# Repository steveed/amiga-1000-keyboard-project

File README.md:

# amiga-1000-keyboard-project
An open source replacement PCB for the Commodore Amiga 1000 keyboard.

The switch plate, generated from the PCB (1.2 mm FR4, version 1):

Renders are regenerated by GitHub Actions whenever the board or plate changes.

## Project Goals
1. Provide a drop-in replacement keyboard PCB for original Amiga 1000 machines.

## Controller
The board takes the original Amiga 1000 keyboard controller (a mask-ROM 6500/1). A 6570 from an
A500/A2000/A3000 keyboard also works if KCLK and KDAT are swapped: solder the cable's white and green
wires into each other's pads on J1. With the original controller: white = KCLK (PA0, pin 38),
green = KDAT (PA1, pin 37), red = +5V, black = GND.

## Rev 2
A second board for the same case that needs no donor controller: an ATmega32U4 with open firmware,
surface-mount parts assembled by the fab, Cherry MX switches, and both the Amiga cable and USB-C
live at once. The first boards have been programmed, and an assembled prototype is fully tested
over USB. See [docs/rev2.md](docs/rev2.md).

## Building
Everything runs in Docker through `make` (KiCad 10 and a small Python image):

- `make print` - 1:1 print sheets in `build/print/` (one 11x17 sheet, or two Letter sheets to tape together).
  Print at 100% / Actual size and check the 100 mm bar.
- `make drc` - refill the pours and fail on any DRC error or schematic/board mismatch.
- `make bom` - regenerate `pcb/bom.csv` from the schematic's Part fields.
- `make fab` - gerbers and drill files, zipped in `build/fab/`.
- `make plate` - the switch plate (DXF and a gerber zip for FR4) in `build/plate/`, generated from the PCB.
- `make case` - the printable case (four STLs and a preview) in `build/case/`, from `case/a1000_case.scad`, for rev 2 (`REV=1` for rev 1). `make case-spacers` fits a rev 2 board in a rev 1 case. See [case/README.md](case/README.md).
- `make keycaps` - rev 2's keycaps in the A1000's sizes (Return, Shifts, `~`, Backspace, Tab; STLs) in `build/case/`, from `case/a1000_keycaps.scad`.
- `make rev2-sch`, `make rev2-pcb`, `make rev2-route`, `make rev2-drc` - the rev 2 board (ATmega32U4, surface mount, Cherry MX). See [pcb/rev_2/README.md](pcb/rev_2/README.md).
- `make firmware`, `make firmware-test` - the rev 2 firmware and its unit tests. See [firmware/README.md](firmware/README.md).
- `make render` - the README renders in `build/render/`.
- `make release` - all of the above, collected in `build/release/`.
- `make rev2-release` - rev 2's order files, plates and firmware, collected in `build/rev2-release/`.

Pushing a `v*` tag runs `make release` on GitHub and publishes rev 1's files as a GitHub release;
pushing a `rev2-v*` tag does the same for rev 2 with `make rev2-release`.

## Reference Material
- [docs/amiga-a1000-schematics-all.pdf](docs/amiga-a1000-schematics-all.pdf) - Amiga 1000 schematics

## Credits
Future revisions are expected to reuse parts of Henryk Richter's [A500KB](https://github.com/HenrykRichter/A500KB) mechanical keyboard. This project uses the same license so that work can be incorporated.

## License
The PCB, its design files and all support code are licensed under [Creative Commons Attribution-NonCommercial-ShareAlike 4.0 International (CC BY-NC-SA 4.0)](https://creativecommons.org/licenses/by-nc-sa/4.0/). See [LICENSE.txt](LICENSE.txt) for the full text.

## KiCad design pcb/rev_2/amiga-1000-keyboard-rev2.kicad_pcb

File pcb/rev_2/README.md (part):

# Rev 2

A surface-mount version of the board that the fab can assemble from stocked parts, for Cherry MX
switches; only the keyswitches and the Caps Lock LED (which sits inside its switch) are fitted by hand. Rev 1, the
through-hole recreation of the original that takes the original 6500/1 controller, stays in `pcb/`.

The outline, mounting holes and switch positions match rev 1, so the case fits both boards; rev 2
needs its own MX plate.

## Schematic

`amiga-1000-keyboard-rev2.kicad_sch` is generated by `tools/gen_rev2_sch.py`: edit the script and
run `make rev2-sch`, which regenerates it and runs ERC. The switches keep rev 1's references and
key names.

- **Controller:** ATmega32U4 at 16 MHz, in place of the mask-ROM 6500/1. Its firmware is
  ported from Henryk Richter's [A500KB](https://github.com/HenrykRichter/A500KB) (AVR, same licence).
  Flashing:
  - first time: the 32U4 ships with Microchip's USB (DFU) bootloader, and a chip with empty flash
    runs straight into it, so it can be flashed over USB as it comes (confirmed on the first boards);
  - updates: the firmware jumps to the bootloader on a key combination, then flash over USB;
  - recovery, if the firmware can't get there: short JP2 (BOOT) while shorting JP1 (RESET), then
    flash over USB; or use the 6-pin ISP header (J3, not fitted; a pogo adapter or a soldered header
    and any AVR programmer), which works even without the bootloader.
- **Amiga and USB both live:** the Amiga cable (J1, same pin order as rev 1's J1: GND, +5V, KCLK,
  KDAT) and a USB-C socket (J2) are on every board. The keyboard works on either, or both at once. Plugging
  both in is safe: the TPS2116 keeps the two 5 V supplies apart (no back-feeding either way), and the
  firmware only pulls KCLK and KDAT while the Amiga's 5 V is present. With both connected, the
  Amiga's and the PC's grounds are joined through the keyboard, as with any USB device.
- **Power:** a TPS2116 power mux. The Amiga's 5 V has priority; USB takes over when it's absent
  (below about 4.3 V), with no diode drop. Its status output (AMIGA_PWR, on PE6) tells the firmware
  whether the Amiga is powered, so it never pulls KCLK or KDAT on a switched-off machine.
- **USB:** USBLC6-2SC6 ESD protection, a 500 mA resettable fuse, 22 R series resistors and the
  5.1 k CC resistors that make it a USB-C device.
- **Matrix:** 8 rows x 12 columns, one diode per key, so any combination of keys reads correctly.
  Each physical row's first 12 keys take electrical rows 0-5; the rest fill rows 6 and 7. SW55
  and SW58 (the international keys) get their own positions; SW92 (short ISO left shift) is fitted
  instead of SW87 and shares its position.

## Switches

Rev 2 takes Cherry MX (and compatible) switches; rev 1 is the Mitsumi replacement. The footprints
come from `tools/gen_mx_fp.py`, in the standard orientation (pins north, LED holes south), with
PCB-mount pegs. Keycap widths come from rev 1's switch spacing. Keys of 2U and wider have PCB-mount
stabiliser holes; the space bar (7.5U) uses a 7U stabiliser (114.3 mm). Return follows Henryk
Richter's US Return for the A500KB: the switch at the key's stem, the centre of the column the cap
has on both rows, with a vertical 2U stabiliser. It suits the US inverted L and the international
Return alike.

SW87 (US 2.5U left Shift) and SW92 (ISO 1.5U short Shift) are alternatives under the same keycaps.
Their facing pegs would be 0.54 mm apart, so SW87 has no west peg and SW92's east peg is a slot
either switch's peg fits.

The Caps Lock LED (D92) is a 3 mm LED through the Caps Lock switch, fitted by hand with it.

## Board

`amiga-1000-keyboard-rev2.kicad_pcb` is generated, then routed:

- `make rev2-pcb` (`tools/gen_rev2_pcb.py`) builds it from rev 1's board and the rev 2 schematic:
  rev 1's outline, stack-up, design rules and GND pours, with rev 2's footprints linked to the
  schematic and placed. The file comes out the same on every run (footprints in reference order,
  UUIDs derived from references), which matters because the router's result depends on file order.
- `make rev2-route` routes it with [KiCadRoutingTools](https://github.com/drandyhaas/KiCadRoutingTools)
  (`tools/route_rev2.py`), following the passes in `tools/rev2_route.json`, then removes the vias
  and tracks left dangling (`tools/rev2_cleanup.py`).
- `make rev2-drc` checks it, schematic parity included.

Placement and routing notes:

- Switches sit at rev 1's key centres; Return at its stem.
- Each key's diode is on the back, between its row and the next, at the first spot that clears every
  pad and hole by 0.5 mm.
- The controller, USB-C and power parts are on the strip behind the keys. USB-C opens to the rear on
  the strip's back edge, about 31 mm right of the case's jack, through its own opening in the
  printed case's back wall. On the first boards it opened to the left out of the step, and the
  plug ran into the jack. The Amiga header (J1) sits on the board's back edge behind the jack.
- U1 sits on the right of the strip, where rev 1's controller was, so the matrix lines run along the
  strip instead of converging mid-board. It's turned so its row pins face the keys, and fanned out: every pin but the crystal and USB data
  pins has a short track to its own via, on two staggered rings. About 20 matrix lines converge on
  this 0.8 mm-pitch chip on two layers, and the router reaches a ring of vias far more easily than
  the pads. A few decoupling caps sit on the back, under it (the diodes already make it a two-sided
  assembly).
- The TPS2116's VIN2 and GND pins have pre-routed escapes too: they're 0.5 mm-pitch pins the router
  kept falling just short of.
- Routing order matters (see `tools/rev2_route.json`): ROW5, the longest run into U1, goes first;
  then VBUS; then the USB and power nets at 0.2 mm clearance (their 0.5 mm-pitch pins are too tight
  for 0.25); then the other rows; then everything else at 0.25 mm, which keeps tracks clear of the
  MX holes; then GND.
- `amiga-1000-keyboard-rev2.kicad_dru` allows the overlaps that are meant (the left Shift
  alternatives, the Caps Lock LED inside its switch, the plate screws between switches) and one
  thermal spoke on GND pads.

### KiCadRoutingTools

`make rev2-route` runs in a `krt:local` image built from a KiCadRoutingTools checkout, with its Rust
router built inside it:

```
FROM python:3.12-slim
WORKDIR /krt
COPY requirements.txt .
RUN pip install --no-cache-dir -r requirements.txt
COPY . .
RUN rm -f rust_router/*.so && python3 build_router.py
```

Build it from the checkout (`docker build -f <that Dockerfile> -t krt:local .`). Routing takes about
five minutes.

## Ordering from JLCPCB

Every push to `main` that touches rev 2 runs the "Rev 2 for JLCPCB" GitHub workflow: DRC and
schematic parity, then gerbers, BOM and placement, uploaded as the artifact
`amiga-1000-keyboard-rev2-jlcpcb`. Locally, `make rev2-fab rev2-jlc` writes the same files to
`build/rev2-fab/` and `build/rev2-jlc/`. Pushing a `rev2-v*` tag publishes the same files, the plates
and the firmware hex as a GitHub release (`make rev2-release`).

- **PCB:** upload `amiga-1000-keyboard-rev2-gerbers.zip`. Two layers, 1.6 mm.
- **Assembly:** both sides (the key diodes and two of U1's decoupling caps are on the back). Upload
  `bom-jlc.csv` and `cpl-jlc.csv`, then check the placement preview: the rotation corrections in
  `tools/jlc_export.py` cover the ICs, but check every part's orientation, especially the diodes and
  U1-U3, before ordering.
- **Parts:** 123 parts in 18 lines, LCSC numbers checked against JLCPCB's parts library. Six are
  Extended parts with a setup fee each (U1, U2, U3, J1, J2 and F1); the rest, all the passives and
  the crystal included, are Basic. The crystal is a 9 pF-load part, so its load caps are 12 pF.
- **Plate:** `amiga-1000-keyboard-rev2-plate-us-gerbers.zip` or `...-plate-iso-gerbers.zip`, as a
  second PCB order: 1.6 mm FR4, no copper needed (the gerbers carry only the outline and mask).
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
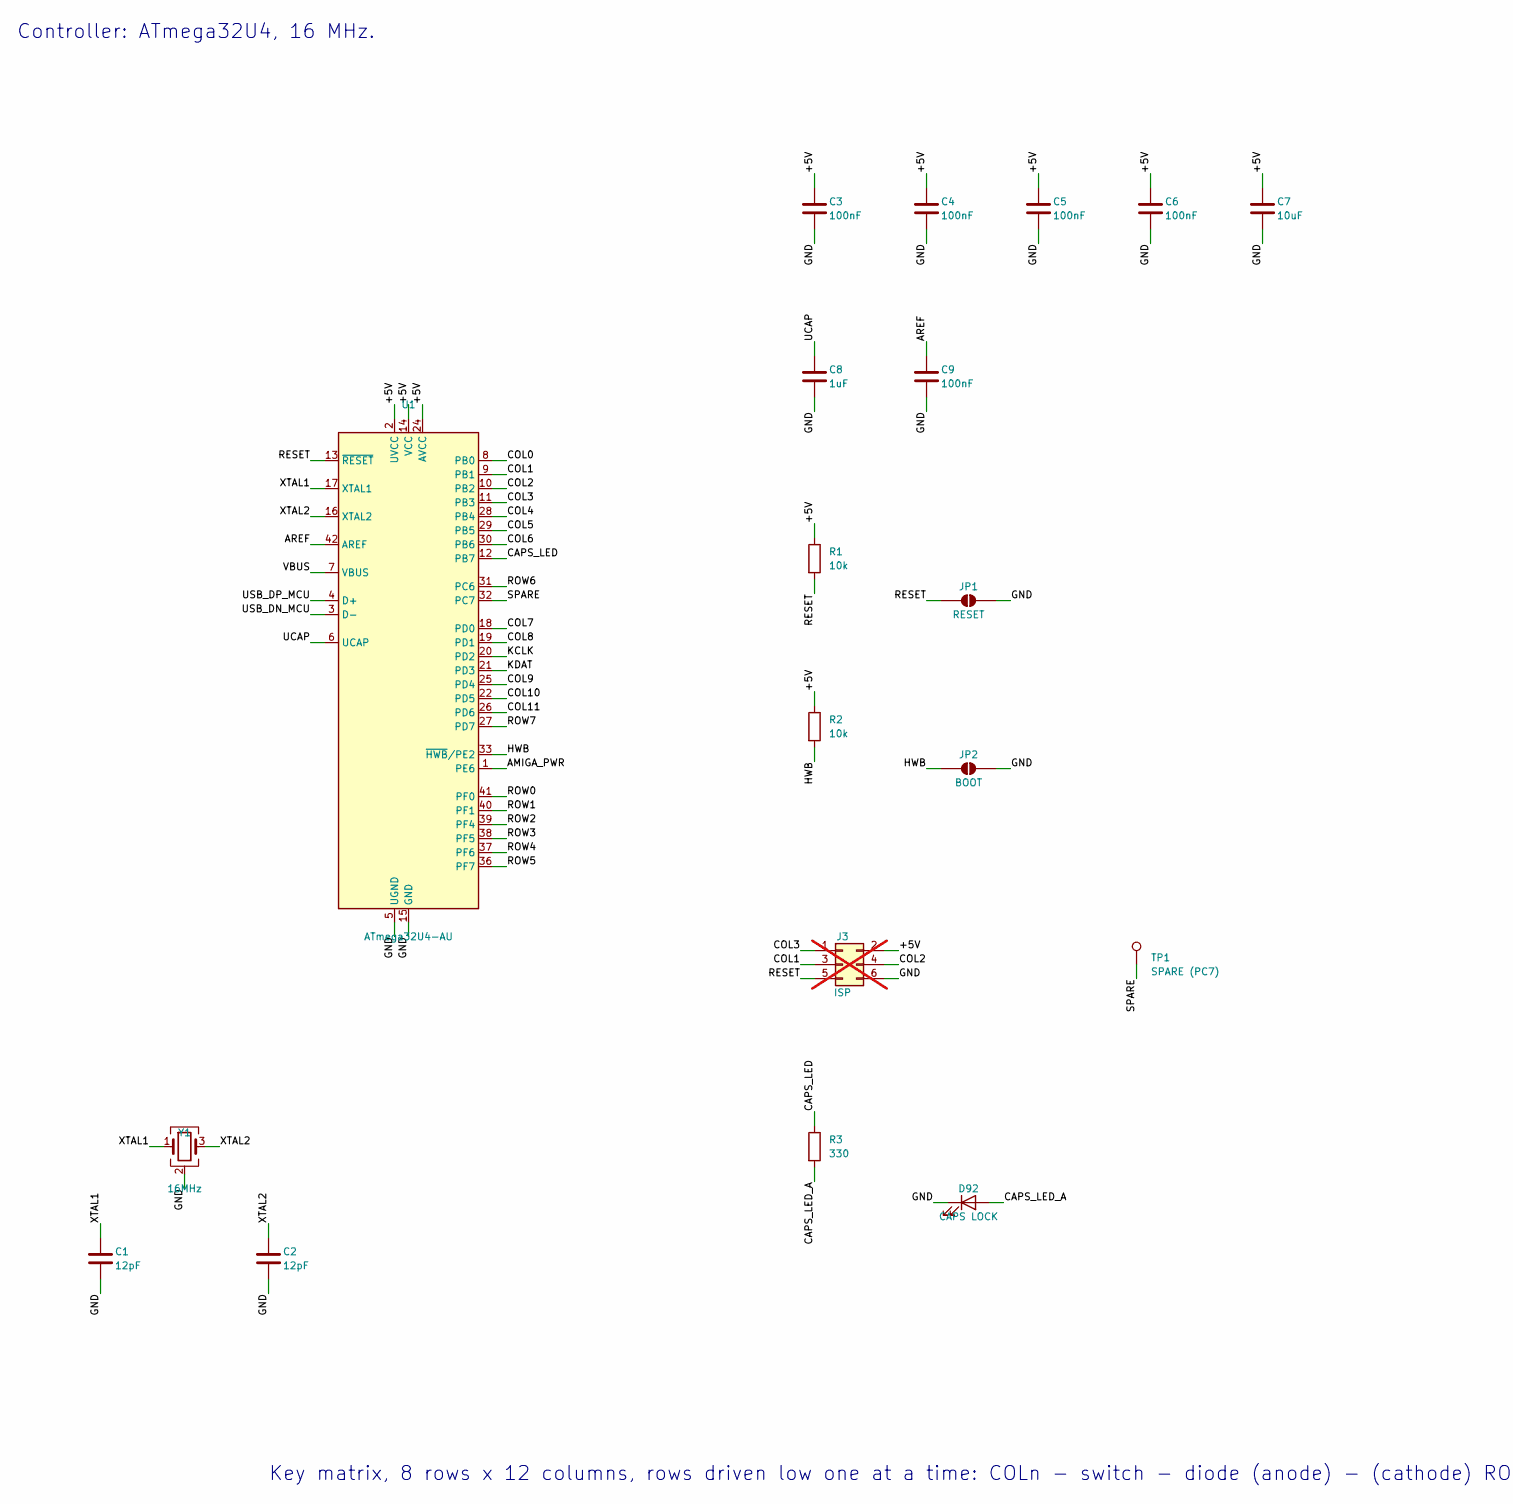
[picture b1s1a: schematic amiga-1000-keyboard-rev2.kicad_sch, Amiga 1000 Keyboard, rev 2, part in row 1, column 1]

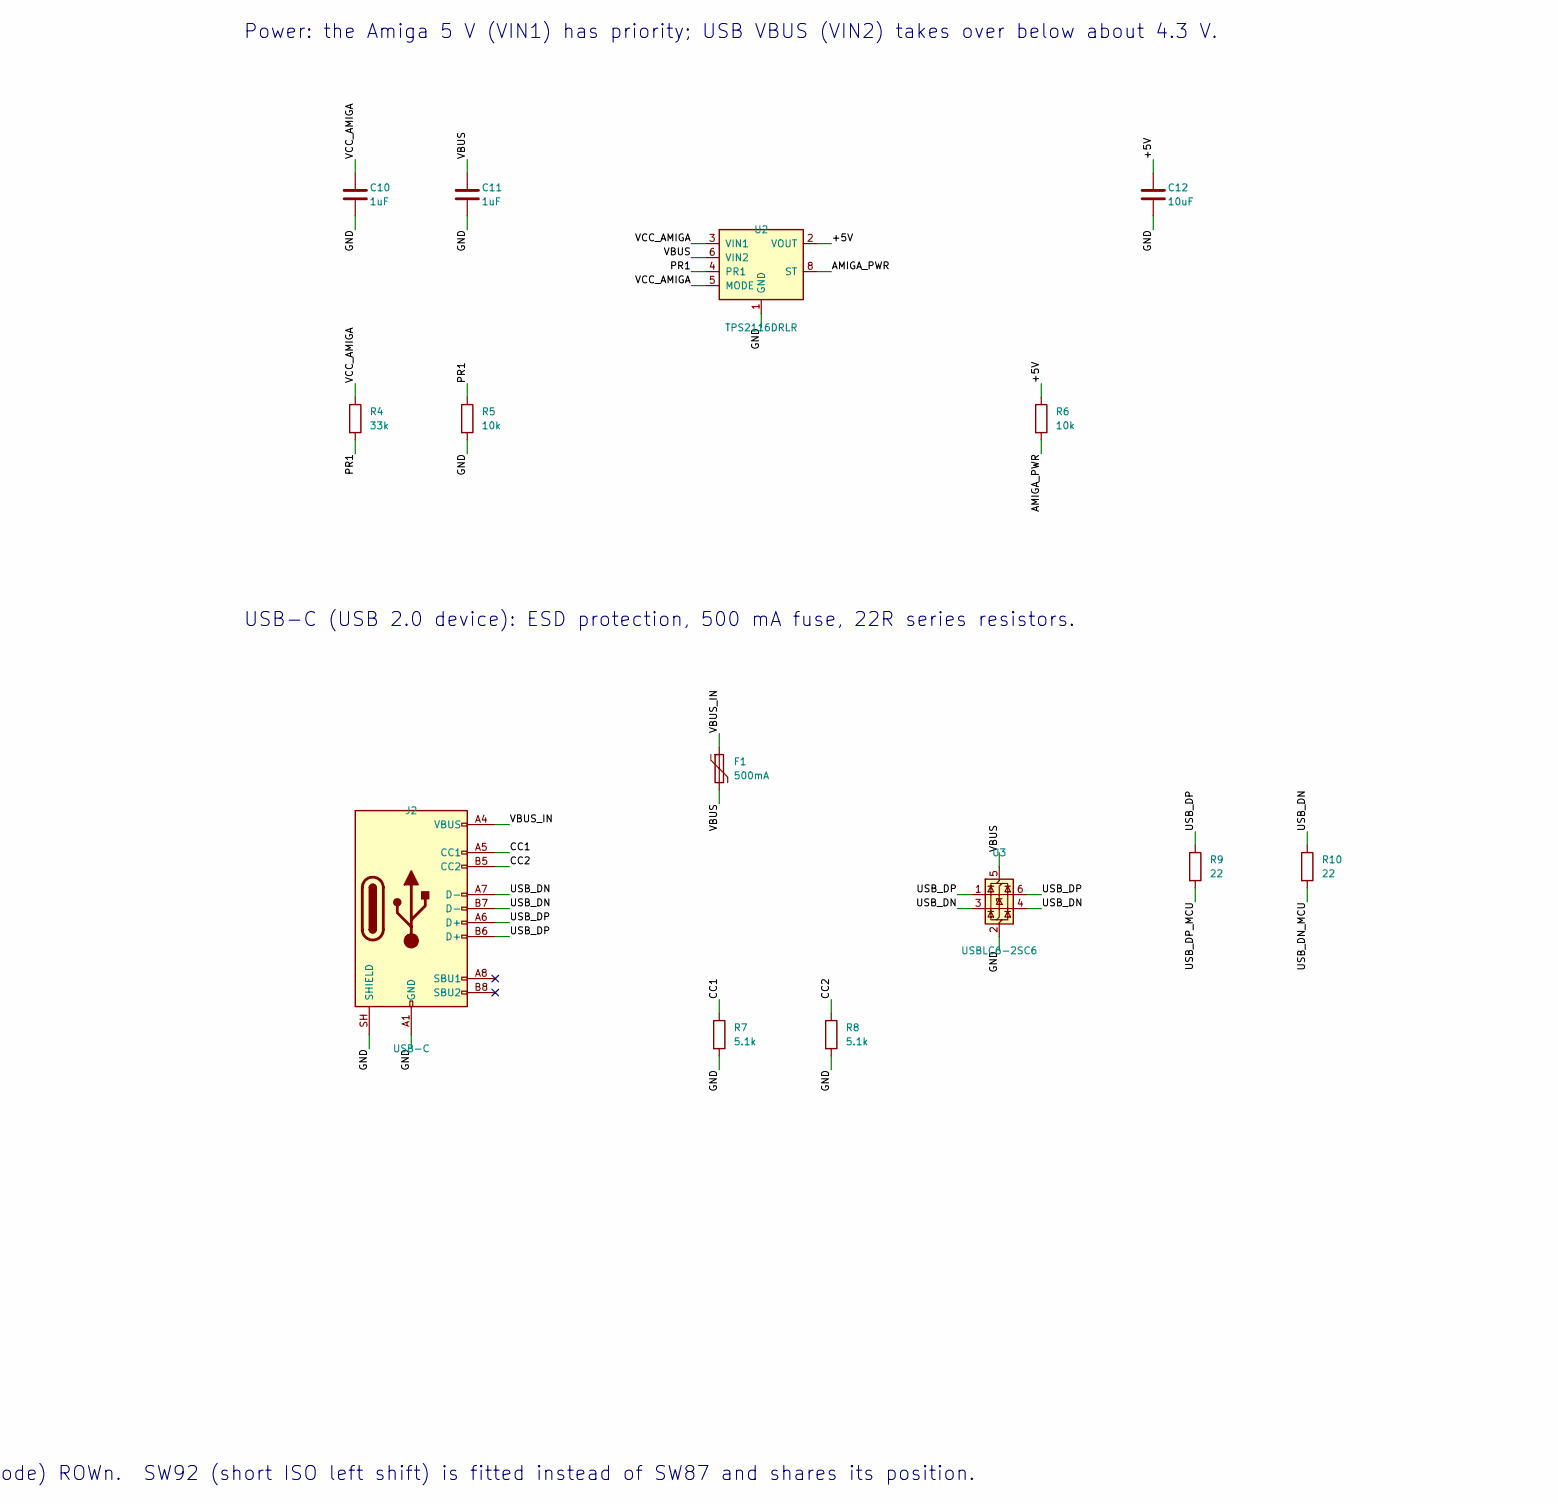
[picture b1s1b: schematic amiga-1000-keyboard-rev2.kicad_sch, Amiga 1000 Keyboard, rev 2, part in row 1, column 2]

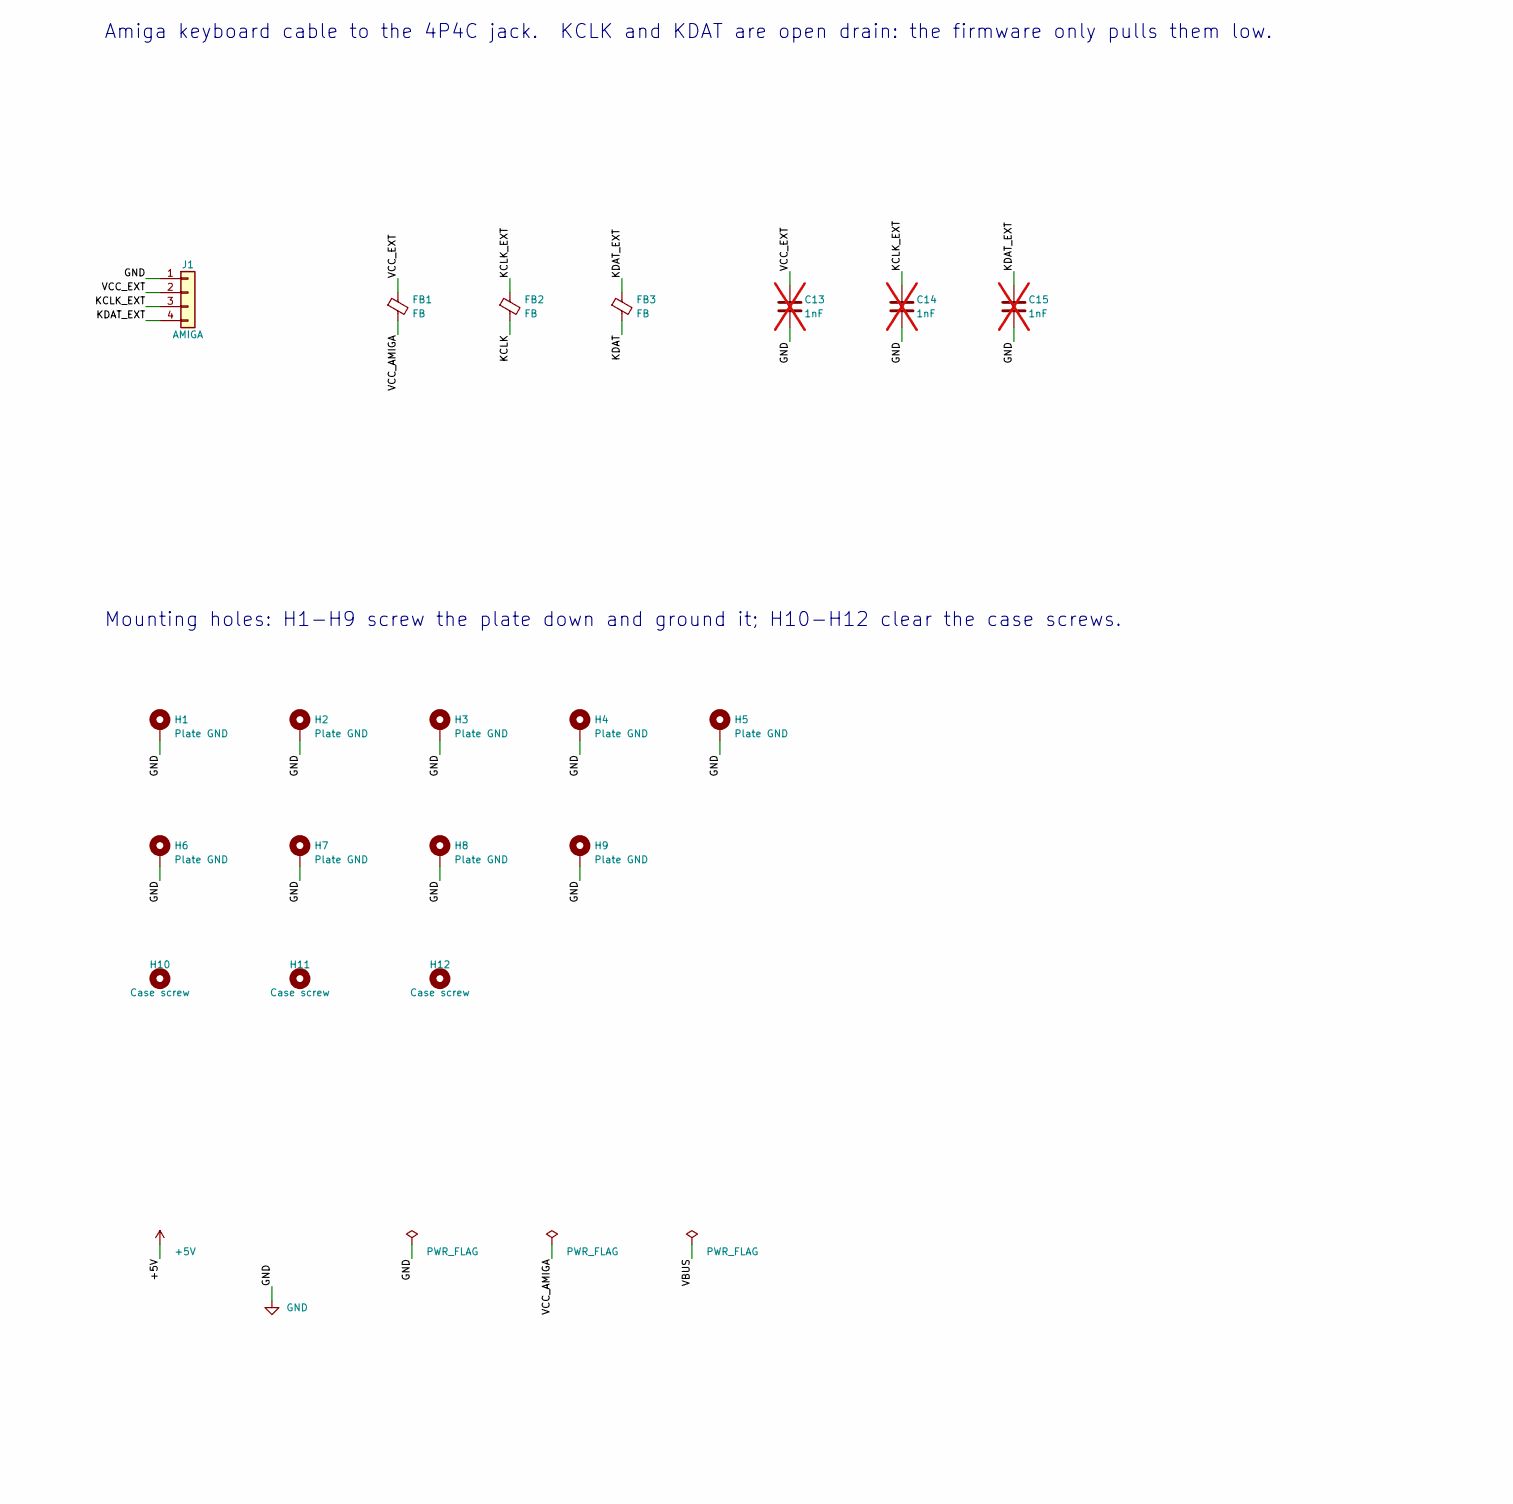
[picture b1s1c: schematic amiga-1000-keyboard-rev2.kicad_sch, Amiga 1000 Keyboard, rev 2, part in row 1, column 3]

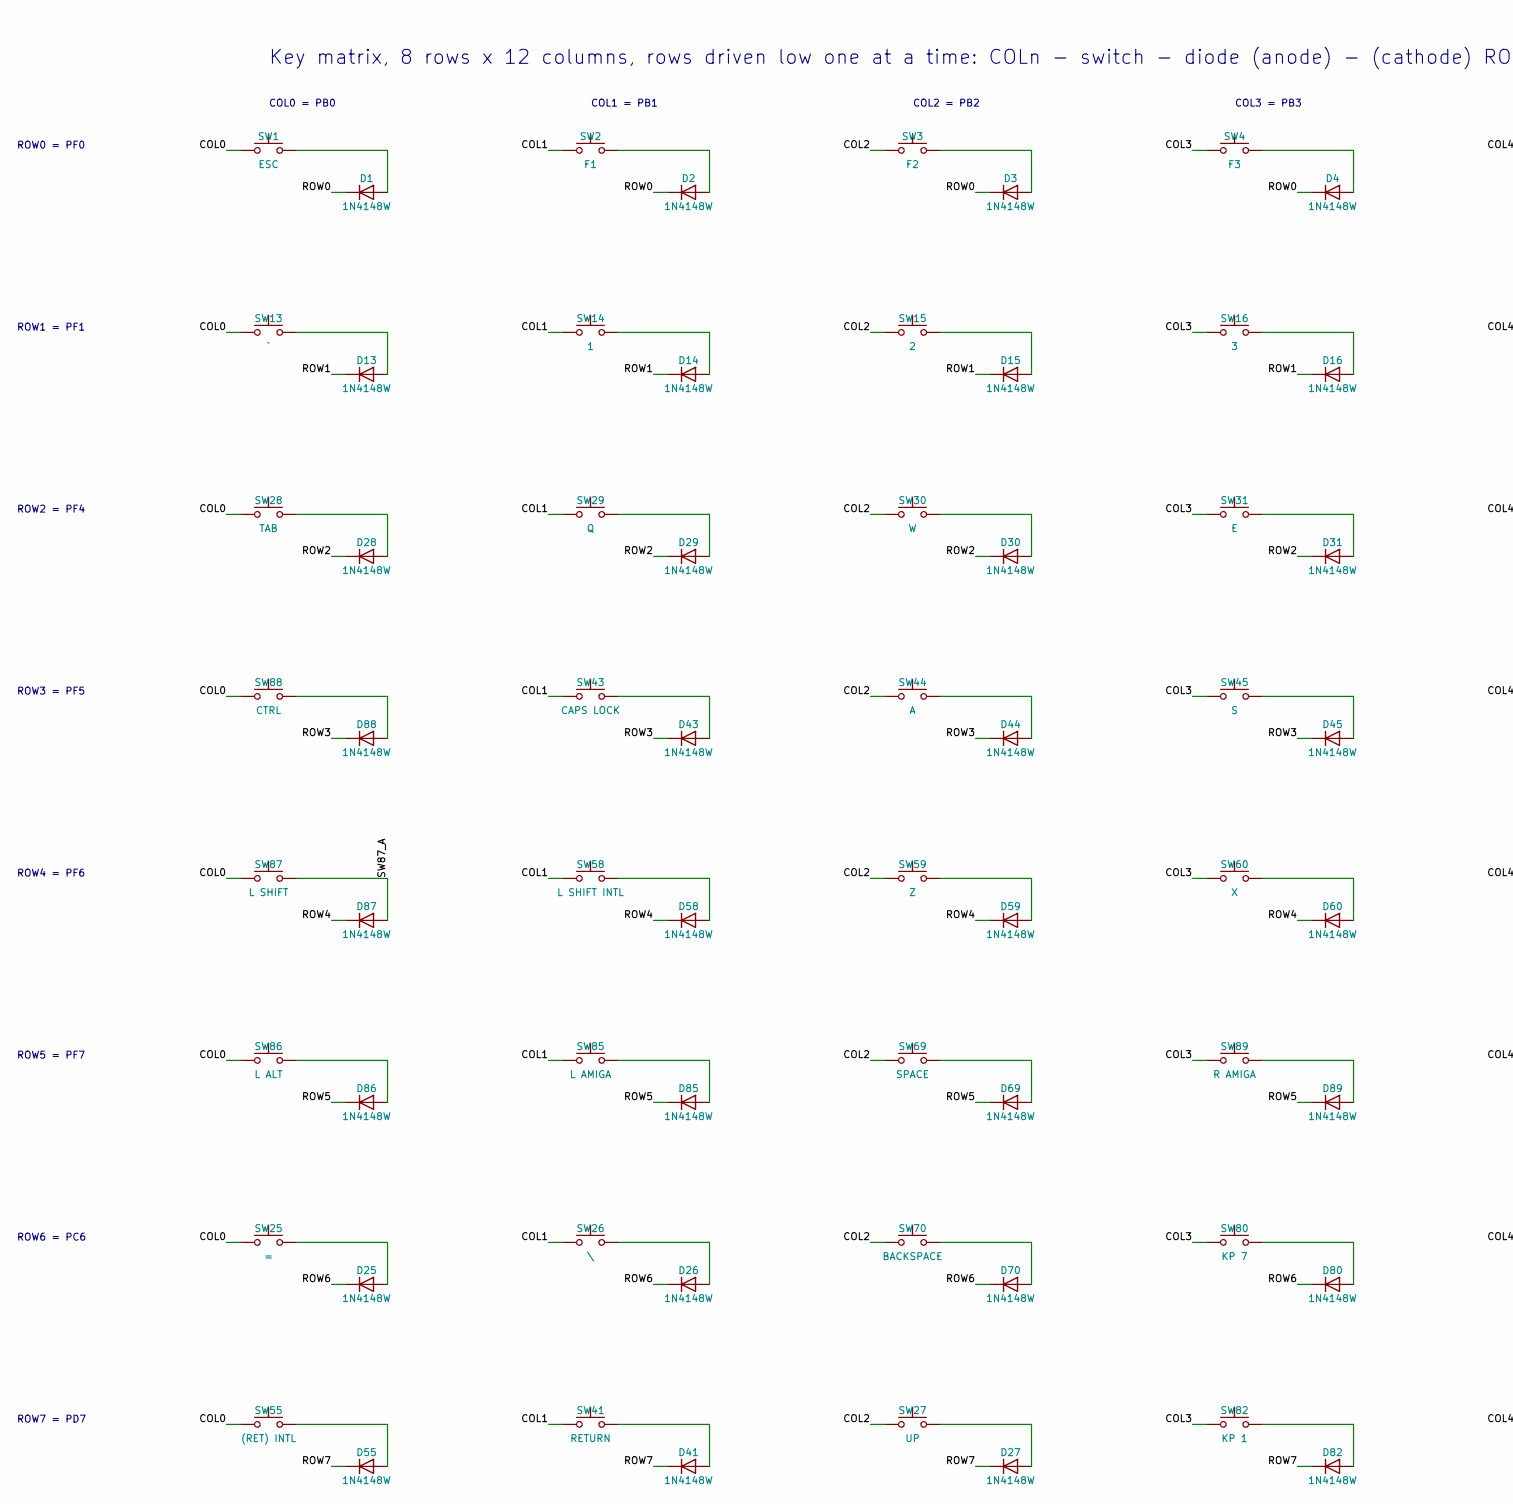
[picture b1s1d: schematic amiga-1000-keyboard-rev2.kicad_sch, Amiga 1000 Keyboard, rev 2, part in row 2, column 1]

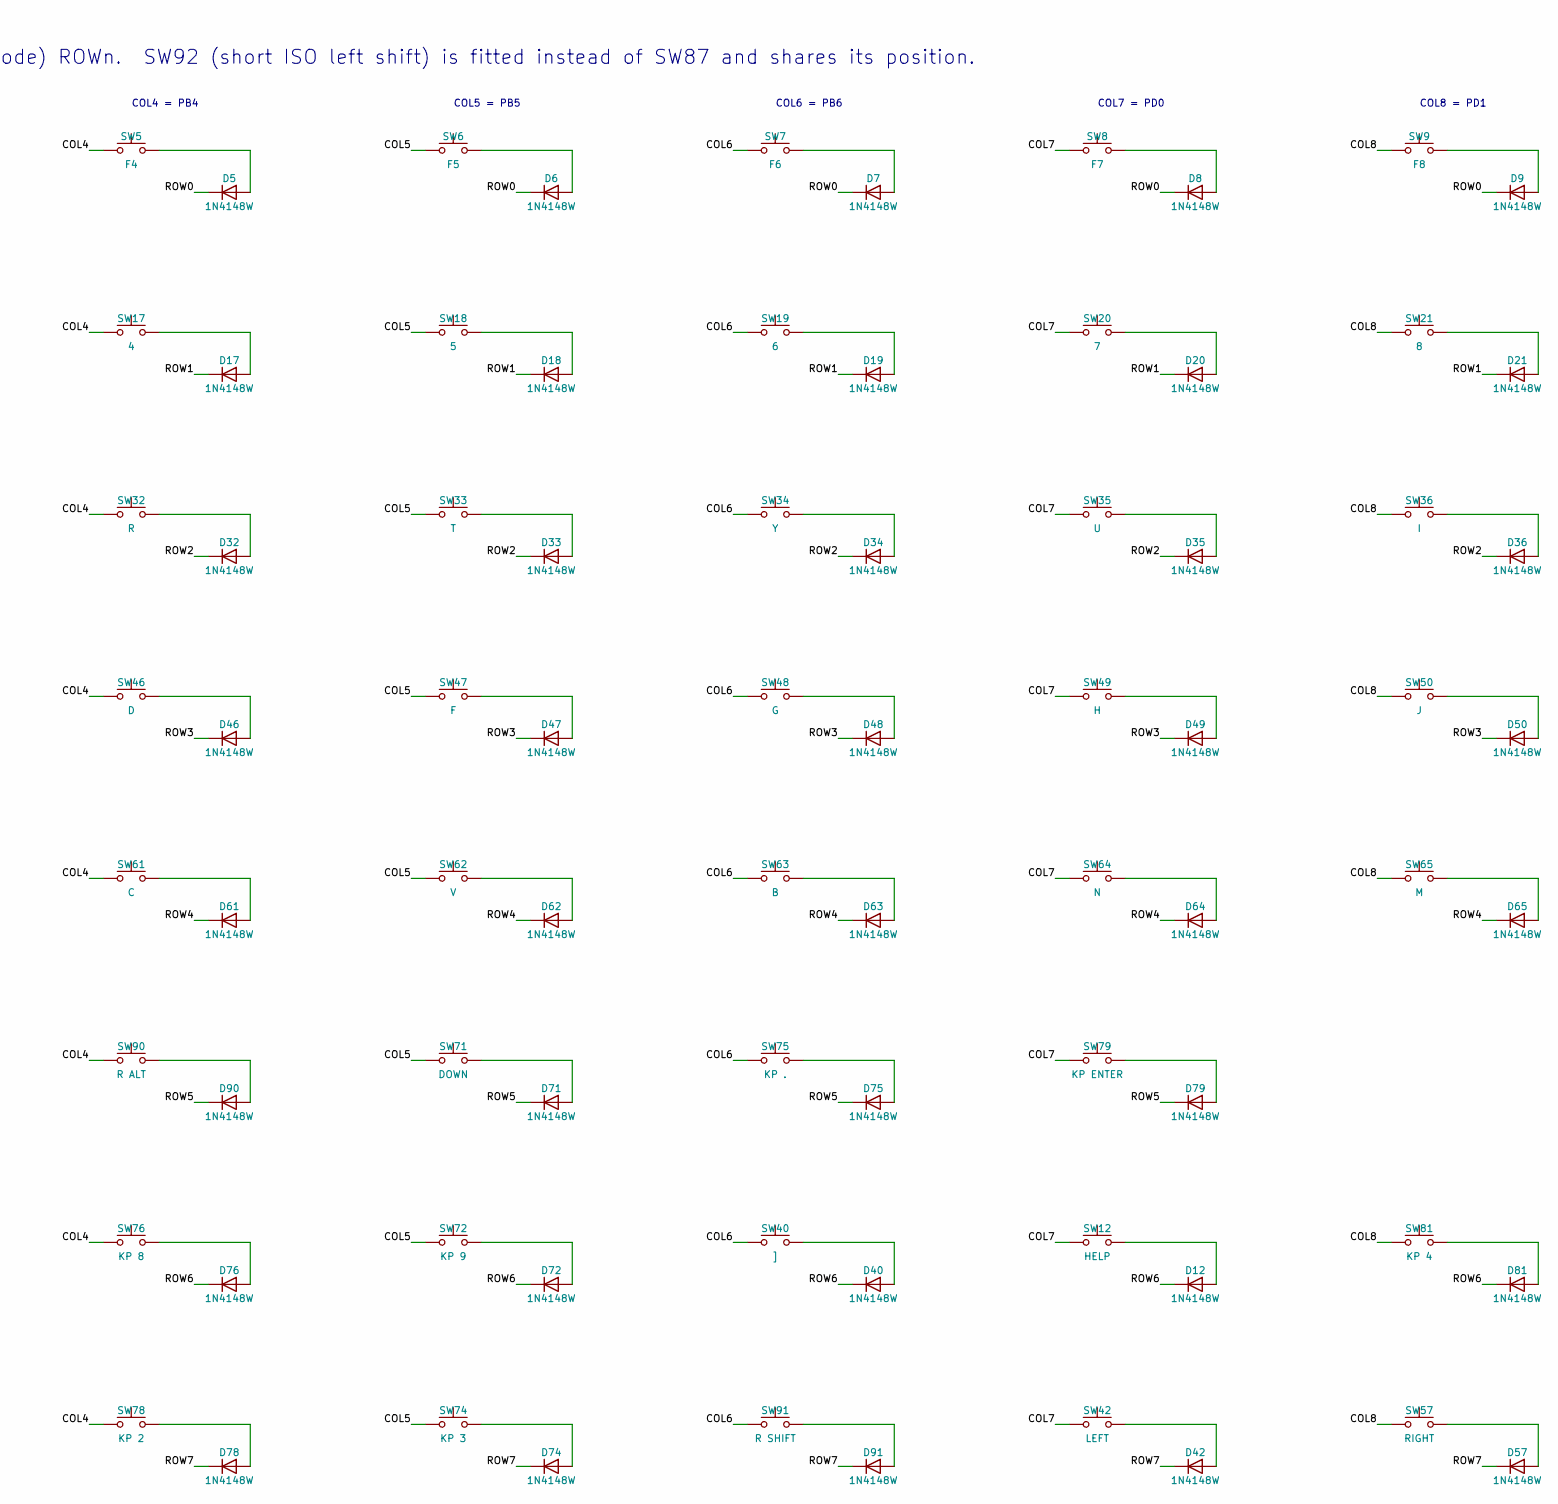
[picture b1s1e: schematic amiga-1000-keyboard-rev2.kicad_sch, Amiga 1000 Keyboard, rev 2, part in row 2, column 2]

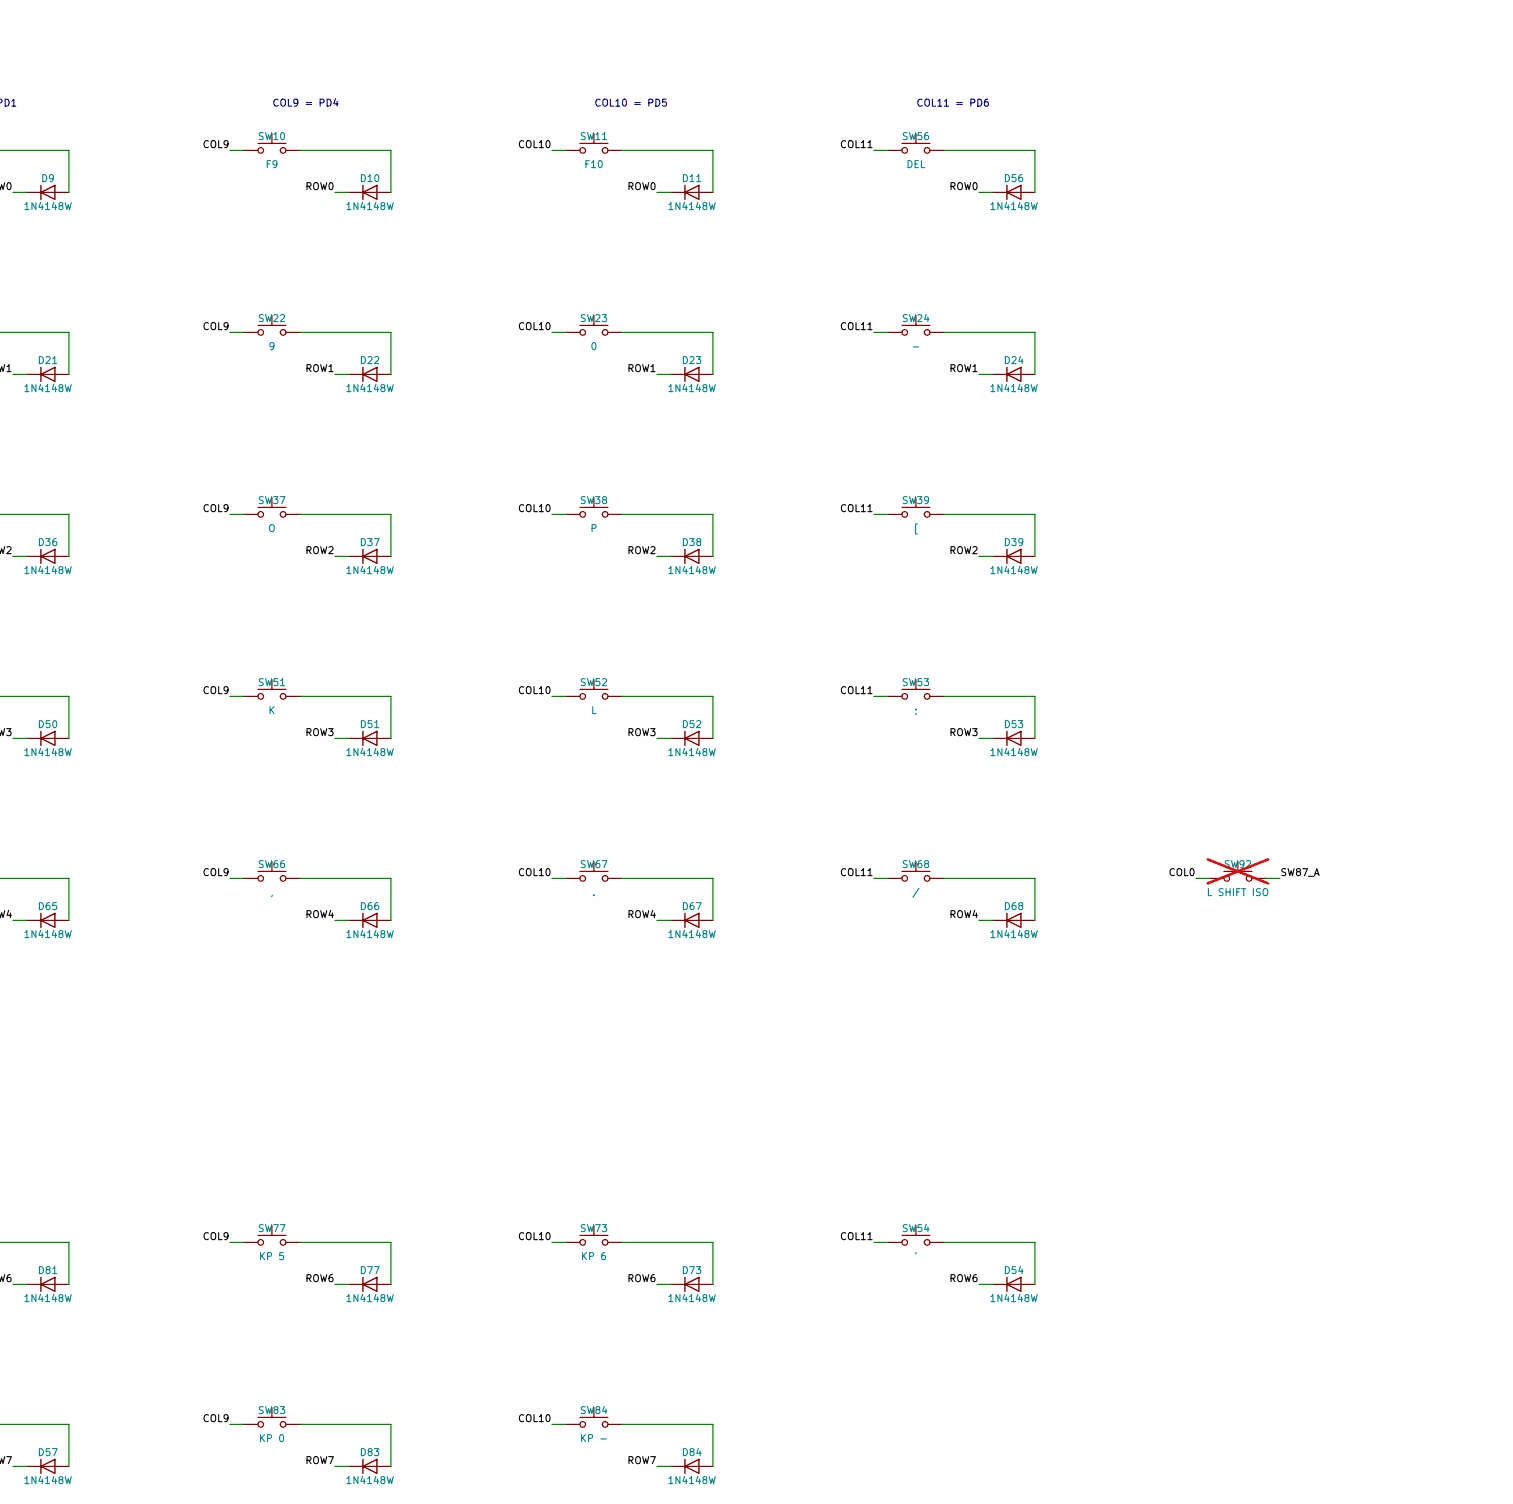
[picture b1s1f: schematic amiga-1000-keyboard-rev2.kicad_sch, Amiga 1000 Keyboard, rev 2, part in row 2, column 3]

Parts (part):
C1, C2: 12pF; C_0402_1005Metric; Part 12 pF C0G 0402; LCSC C1547
C3, C4, C5, C6, C9: 100nF; C_0402_1005Metric; Part 100 nF X7R 0402; LCSC C1525
C7, C12: 10uF; C_0603_1608Metric; Part 10 uF X5R 10 V 0603; LCSC C19702
C8: 1uF; C_0402_1005Metric; Part 1 uF X5R 0402; LCSC C52923
C10, C11: 1uF; C_0402_1005Metric; Part 1 uF X5R 10 V 0402; LCSC C52923
C13, C14, C15: 1nF; C_0402_1005Metric; Part 1 nF X7R 0402; LCSC C1523; not fitted
D1, D2, D3, D4, D5, D6, D7, D8, D9, D10, D11, D12, D13, D14, D15, D16, D17, D18, D19, D20, D21, D22, D23, D24, D25, D26, D27, D28, D29, D30, D31, D32, D33, D34, D35, D36, D37, D38, D39, D40, D41, D42, D43, D44, D45, D46, D47, D48, D49, D50, D51, D52, D53, D54, D55, D56, D57, D58, D59, D60, D61, D62, D63, D64, D65, D66, D67, D68, D69, D70, D71, D72, D73, D74, D75, D76, D77, D78, D79, D80, D81, D82, D83, D84, D85, D86, D87, D88, D89, D90, D91: 1N4148W; D_SOD-123; Part 1N4148W SOD-123; LCSC C81598
D92: CAPS LOCK; MX_A1000_LED; Part 3 mm LED through a Cherry MX switch
F1: 500mA; Fuse_1206_3216Metric; Part 500 mA hold PTC fuse, 1206; LCSC C70077
FB1, FB2, FB3: FB; L_0603_1608Metric; Part Ferrite bead 600R@100MHz 0603; LCSC C1002
H1, H2, H3, H4, H5, H6, H7, H8, H9: Plate GND; MountingHole_3.8mm_Plate_GND
H10, H11, H12: Case screw; MountingHole_7.5mm_CaseClearance
J1: AMIGA; JST_PH_S4B-PH-SM4-TB_1x04-1MP_P2.00mm_Horizontal; Part JST PH 4-pin SMD right angle; LCSC C265102
J2: USB-C; USB_C_Receptacle_HRO_TYPE-C-31-M-12; Part HRO TYPE-C-31-M-12 USB-C receptacle; LCSC C165948
J3: ISP; PinHeader_2x03_P2.54mm_Vertical; Part AVR ISP header (recovery only); not fitted
JP1: RESET; SolderJumper-2_P1.3mm_Open_RoundedPad1.0x1.5mm; Part pads, shorted with tweezers
JP2: BOOT; SolderJumper-2_P1.3mm_Open_RoundedPad1.0x1.5mm; Part pads, shorted with tweezers
R1, R2, R5, R6: 10k; R_0402_1005Metric; Part 10k 1% 0402; LCSC C25744
R3: 330; R_0402_1005Metric; Part 330 1% 0402; LCSC C25104
R4: 33k; R_0402_1005Metric; Part 33k 1% 0402; LCSC C25779
R7, R8: 5.1k; R_0402_1005Metric; Part 5.1k 1% 0402; LCSC C25905
R9, R10: 22; R_0402_1005Metric; Part 22 1% 0402; LCSC C25092
SW1: ESC; MX_A1000_1U; Part Cherry MX (or compatible) keyswitch
SW2: F1; MX_A1000_1.25U; Part Cherry MX (or compatible) keyswitch
SW3: F2; MX_A1000_1.25U; Part Cherry MX (or compatible) keyswitch
SW4: F3; MX_A1000_1.25U; Part Cherry MX (or compatible) keyswitch
SW5: F4; MX_A1000_1.25U; Part Cherry MX (or compatible) keyswitch
SW6: F5; MX_A1000_1.25U; Part Cherry MX (or compatible) keyswitch
SW7: F6; MX_A1000_1.25U; Part Cherry MX (or compatible) keyswitch
SW8: F7; MX_A1000_1.25U; Part Cherry MX (or compatible) keyswitch
SW9: F8; MX_A1000_1.25U; Part Cherry MX (or compatible) keyswitch
SW10: F9; MX_A1000_1.25U; Part Cherry MX (or compatible) keyswitch
SW11: F10; MX_A1000_1.25U; Part Cherry MX (or compatible) keyswitch
SW12: HELP; MX_A1000_1U; Part Cherry MX (or compatible) keyswitch
SW13: `; MX_A1000_1.25U; Part Cherry MX (or compatible) keyswitch
SW14: 1; MX_A1000_1U; Part Cherry MX (or compatible) keyswitch
SW15: 2; MX_A1000_1U; Part Cherry MX (or compatible) keyswitch
SW16: 3; MX_A1000_1U; Part Cherry MX (or compatible) keyswitch
SW17: 4; MX_A1000_1U; Part Cherry MX (or compatible) keyswitch
SW18: 5; MX_A1000_1U; Part Cherry MX (or compatible) keyswitch
SW19: 6; MX_A1000_1U; Part Cherry MX (or compatible) keyswitch
SW20: 7; MX_A1000_1U; Part Cherry MX (or compatible) keyswitch
SW21: 8; MX_A1000_1U; Part Cherry MX (or compatible) keyswitch
SW22: 9; MX_A1000_1U; Part Cherry MX (or compatible) keyswitch
SW23: 0; MX_A1000_1U; Part Cherry MX (or compatible) keyswitch
SW24: -; MX_A1000_1U; Part Cherry MX (or compatible) keyswitch
SW25: =; MX_A1000_1U; Part Cherry MX (or compatible) keyswitch
SW26: \; MX_A1000_1U; Part Cherry MX (or compatible) keyswitch
SW27: UP; MX_A1000_1U; Part Cherry MX (or compatible) keyswitch
SW28: TAB; MX_A1000_1.75U; Part Cherry MX (or compatible) keyswitch
SW29: Q; MX_A1000_1U; Part Cherry MX (or compatible) keyswitch
SW30: W; MX_A1000_1U; Part Cherry MX (or compatible) keyswitch
SW31: E; MX_A1000_1U; Part Cherry MX (or compatible) keyswitch
SW32: R; MX_A1000_1U; Part Cherry MX (or compatible) keyswitch
SW33: T; MX_A1000_1U; Part Cherry MX (or compatible) keyswitch
SW34: Y; MX_A1000_1U; Part Cherry MX (or compatible) keyswitch
SW35: U; MX_A1000_1U; Part Cherry MX (or compatible) keyswitch
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
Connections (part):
+5V: C3.1, C4.1, C5.1, C6.1, C7.1, C12.1, J3.2, R1.1, R2.1, R6.1, U1.2 (UVCC), U1.14 (VCC), U1.24 (AVCC), U1.34 (VCC), U1.44 (AVCC), U2.2 (VOUT), U2.7 (VOUT)
/AMIGA_PWR: R6.2, U1.1 (PE6), U2.8 (ST)
/AREF: C9.1, U1.42 (AREF)
/CAPS_LED: R3.1, U1.12 (PB7)
/CAPS_LED_A: D92.2 (A), R3.2
/CC1: J2.A5 (CC1), R7.1
/CC2: J2.B5 (CC2), R8.1
/COL0: SW1.1, SW13.1, SW25.1, SW28.1, SW55.1, SW86.1, SW87.1, SW88.1, SW92.1, U1.8 (PB0)
/COL1: J3.3, SW2.1, SW14.1, SW26.1, SW29.1, SW41.1, SW43.1, SW58.1, SW85.1, U1.9 (PB1)
/COL2: J3.4, SW3.1, SW15.1, SW27.1, SW30.1, SW44.1, SW59.1, SW69.1, SW70.1, U1.10 (PB2)
/COL3: J3.1, SW4.1, SW16.1, SW31.1, SW45.1, SW60.1, SW80.1, SW82.1, SW89.1, U1.11 (PB3)
/COL4: SW5.1, SW17.1, SW32.1, SW46.1, SW61.1, SW76.1, SW78.1, SW90.1, U1.28 (PB4)
/COL5: SW6.1, SW18.1, SW33.1, SW47.1, SW62.1, SW71.1, SW72.1, SW74.1, U1.29 (PB5)
/COL6: SW7.1, SW19.1, SW34.1, SW40.1, SW48.1, SW63.1, SW75.1, SW91.1, U1.30 (PB6)
/COL7: SW8.1, SW12.1, SW20.1, SW35.1, SW42.1, SW49.1, SW64.1, SW79.1, U1.18 (PD0)
/COL8: SW9.1, SW21.1, SW36.1, SW50.1, SW57.1, SW65.1, SW81.1, U1.19 (PD1)
/COL9: SW10.1, SW22.1, SW37.1, SW51.1, SW66.1, SW77.1, SW83.1, U1.25 (PD4)
/COL10: SW11.1, SW23.1, SW38.1, SW52.1, SW67.1, SW73.1, SW84.1, U1.22 (PD5)
/COL11: SW24.1, SW39.1, SW53.1, SW54.1, SW56.1, SW68.1, U1.26 (PD6)
/HWB: JP2.1 (A), R2.2, U1.33 (~HWB/PE2)
/KCLK: FB2.2, U1.20 (PD2)
/KCLK_EXT: C14.1, FB2.1, J1.3
/KDAT: FB3.2, U1.21 (PD3)
/KDAT_EXT: C15.1, FB3.1, J1.4
/PR1: R4.2, R5.1, U2.4 (PR1)
/RESET: J3.5, JP1.1 (A), R1.2, U1.13 (~RESET)
/ROW0: D1.1 (K), D2.1 (K), D3.1 (K), D4.1 (K), D5.1 (K), D6.1 (K), D7.1 (K), D8.1 (K), D9.1 (K), D10.1 (K), D11.1 (K), D56.1 (K), U1.41 (PF0)
/ROW1: D13.1 (K), D14.1 (K), D15.1 (K), D16.1 (K), D17.1 (K), D18.1 (K), D19.1 (K), D20.1 (K), D21.1 (K), D22.1 (K), D23.1 (K), D24.1 (K), U1.40 (PF1)
/ROW2: D28.1 (K), D29.1 (K), D30.1 (K), D31.1 (K), D32.1 (K), D33.1 (K), D34.1 (K), D35.1 (K), D36.1 (K), D37.1 (K), D38.1 (K), D39.1 (K), U1.39 (PF4)
/ROW3: D43.1 (K), D44.1 (K), D45.1 (K), D46.1 (K), D47.1 (K), D48.1 (K), D49.1 (K), D50.1 (K), D51.1 (K), D52.1 (K), D53.1 (K), D88.1 (K), U1.38 (PF5)
/ROW4: D58.1 (K), D59.1 (K), D60.1 (K), D61.1 (K), D62.1 (K), D63.1 (K), D64.1 (K), D65.1 (K), D66.1 (K), D67.1 (K), D68.1 (K), D87.1 (K), U1.37 (PF6)
/ROW5: D69.1 (K), D71.1 (K), D75.1 (K), D79.1 (K), D85.1 (K), D86.1 (K), D89.1 (K), D90.1 (K), U1.36 (PF7)
/ROW6: D12.1 (K), D25.1 (K), D26.1 (K), D40.1 (K), D54.1 (K), D70.1 (K), D72.1 (K), D73.1 (K), D76.1 (K), D77.1 (K), D80.1 (K), D81.1 (K), U1.31 (PC6)
/ROW7: D27.1 (K), D41.1 (K), D42.1 (K), D55.1 (K), D57.1 (K), D74.1 (K), D78.1 (K), D82.1 (K), D83.1 (K), D84.1 (K), D91.1 (K), U1.27 (PD7)
/SPARE: TP1.1, U1.32 (PC7)
/SW87_A: D87.2 (A), SW87.2, SW92.2
/UCAP: C8.1, U1.6 (UCAP)
/USB_DN: J2.A7 (D-), J2.B7 (D-), R10.1, U3.3 (I/O2), U3.4 (I/O2)
/USB_DN_MCU: R10.2, U1.3 (D-)
/USB_DP: J2.A6 (D+), J2.B6 (D+), R9.1, U3.1 (I/O1), U3.6 (I/O1)
/USB_DP_MCU: R9.2, U1.4 (D+)
/VBUS: C11.1, F1.2, U1.7 (VBUS), U2.6 (VIN2), U3.5 (VBUS)
/VBUS_IN: F1.1, J2.A4 (VBUS), J2.A9 (VBUS), J2.B4 (VBUS), J2.B9 (VBUS)
/VCC_AMIGA: C10.1, FB1.2, R4.1, U2.3 (VIN1), U2.5 (MODE)
/VCC_EXT: C13.1, FB1.1, J1.2
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
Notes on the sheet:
Controller: ATmega32U4, 16 MHz.
Power: the Amiga 5 V (VIN1) has priority; USB VBUS (VIN2) takes over below about 4.3 V.
USB-C (USB 2.0 device): ESD protection, 500 mA fuse, 22R series resistors.
Amiga keyboard cable to the 4P4C jack. KCLK and KDAT are open drain: the firmware only pulls them low.
Mounting holes: H1-H9 screw the plate down and ground it; H10-H12 clear the case screws.
Key matrix, 8 rows x 12 columns, rows driven low one at a time: COLn - switch - diode (anode) - (cathode) ROWn. SW92 (short ISO left shift) is fitted instead of SW87 and shares its position.
ROW0 = PF0
ROW1 = PF1
ROW2 = PF4
ROW3 = PF5
ROW4 = PF6
ROW5 = PF7
ROW6 = PC6
ROW7 = PD7
COL0 = PB0
COL1 = PB1
COL2 = PB2
COL3 = PB3
COL4 = PB4
COL5 = PB5
COL6 = PB6
COL7 = PD0
COL8 = PD1
COL9 = PD4
COL10 = PD5
COL11 = PD6

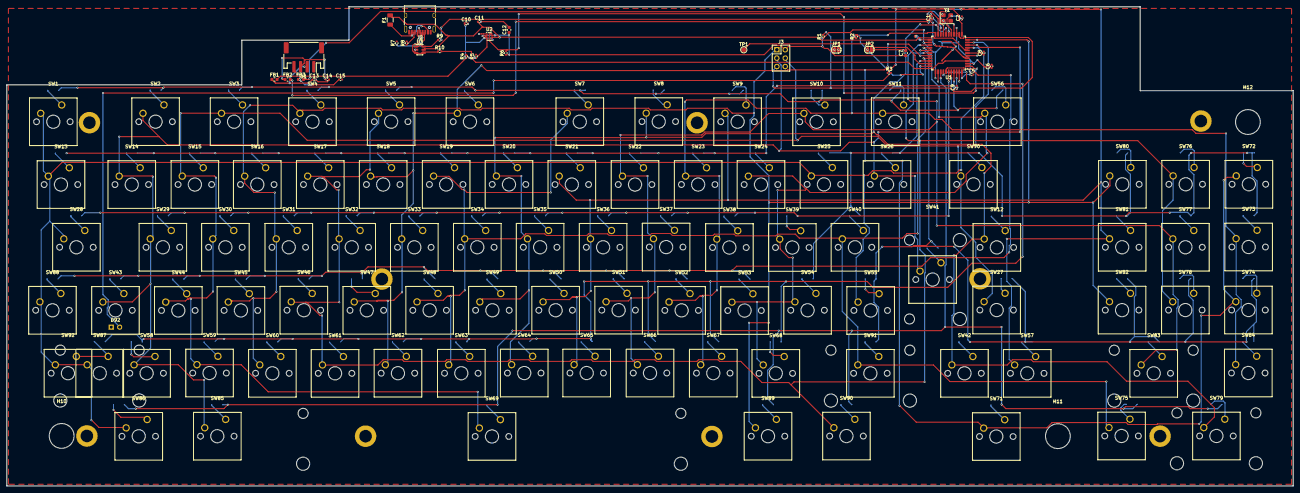
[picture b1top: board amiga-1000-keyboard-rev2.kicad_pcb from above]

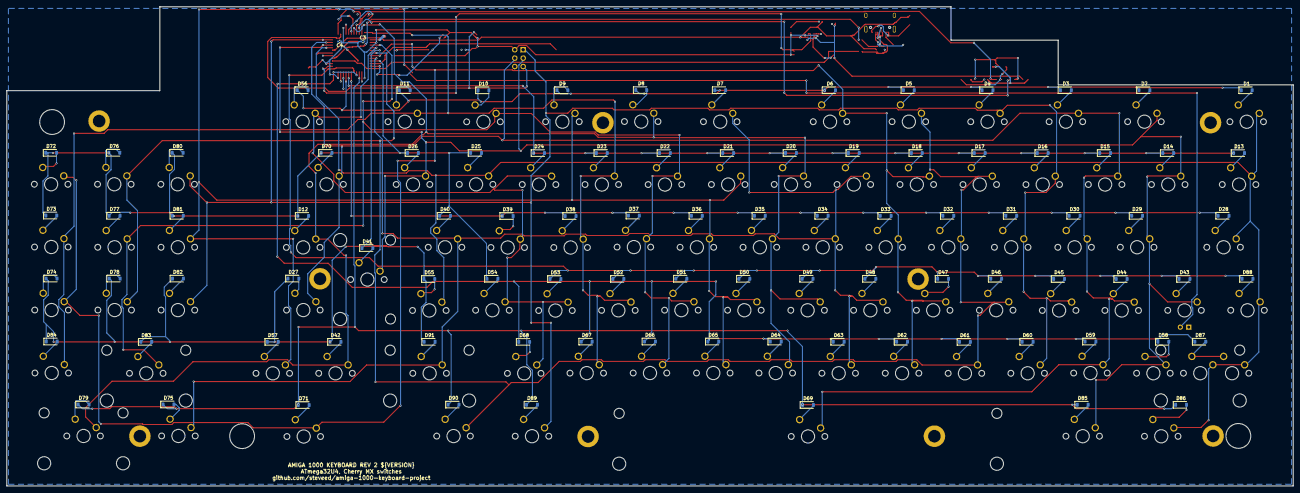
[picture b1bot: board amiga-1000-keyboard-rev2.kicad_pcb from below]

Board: 2 copper layers, 389.2 x 145.0 mm, 235 parts (93 on the bottom side), 138 nets.

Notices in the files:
pcb/amiga-1000-keyboard.kicad_pcb:
License: CC BY-NC-SA 4.0
